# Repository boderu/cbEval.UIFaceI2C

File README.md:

# cbEval.UIFaceI2C
I2C-Bus User-Interface für das Camdenboss-System.

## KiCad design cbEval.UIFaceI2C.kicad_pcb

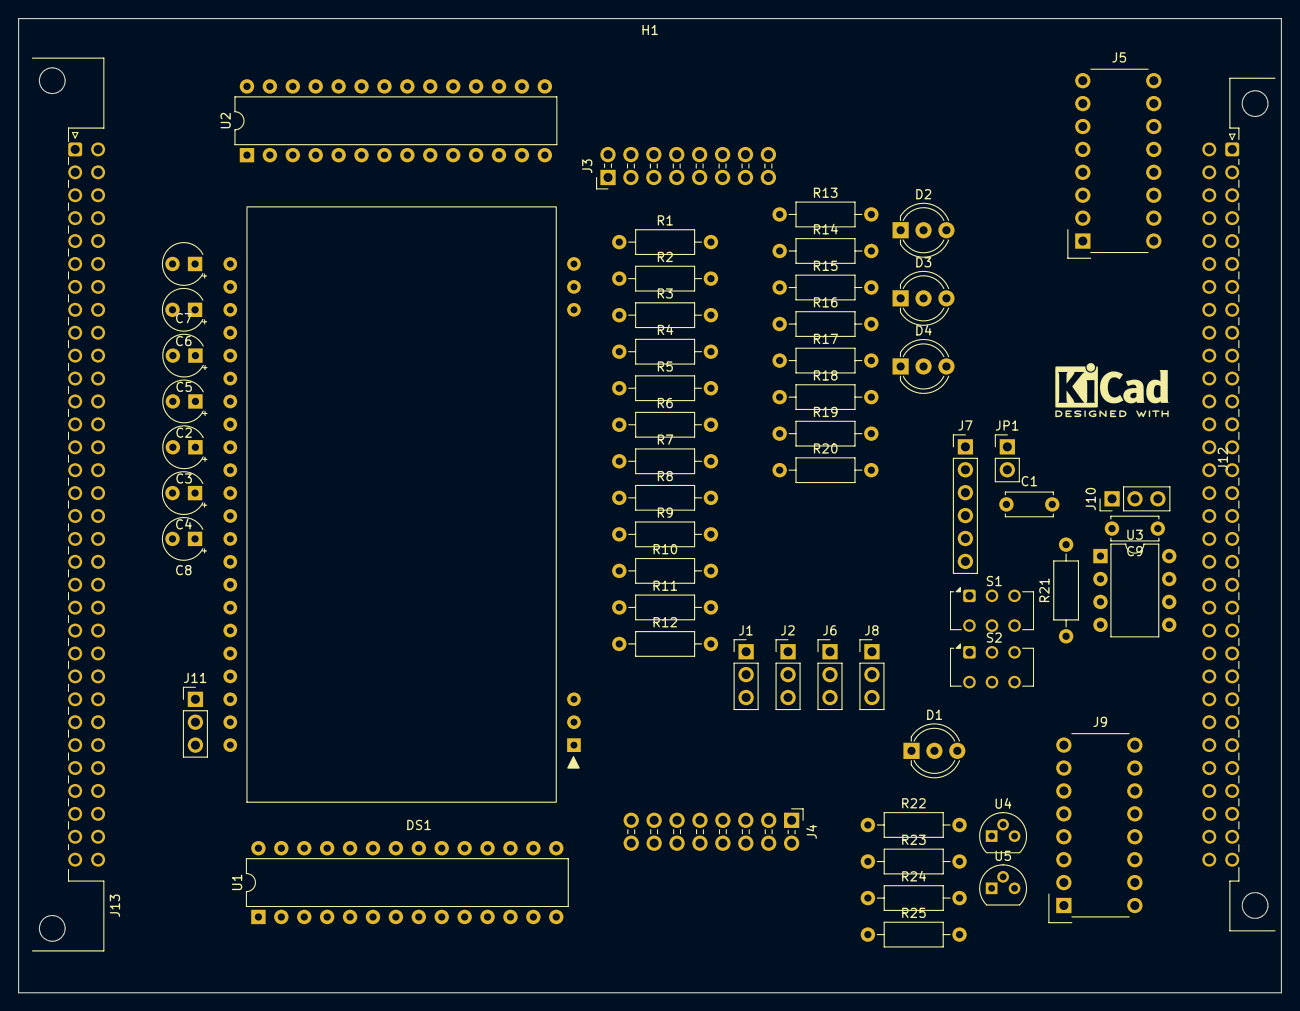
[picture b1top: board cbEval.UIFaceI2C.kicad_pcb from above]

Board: 2 copper layers, 140.0 x 108.0 mm, 62 parts (0 on the bottom side), 59 nets, no tracks yet.

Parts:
C1: 4n7; C_Disc_D5.0mm_W2.5mm_P5.08mm
C2, C3, C4, C5, C6, C7, C8: 1µ; CP_Radial_Tantal_D4.5mm_P2.50mm
C9: 100n; C_Disc_D5.0mm_W2.5mm_P5.08mm
D1, D2, D3, D4: MV5439A; LED_D5.0mm-3
DS1: EA DOGM204W-A; EA-DOGM204-A
H1: CIME.E.BE3500S.4x; Camdenboss.CIME.E.BE3500S.4x
J1, J2, J6, J8, J10, J11: Bergstik-II_1x3; PinHeader_1x03_P2.54mm_Vertical
J3, J4: Header.Hor.2x8.9-103326-0-08; PinHeader_2x08_P2.54mm_Horizontal
J5, J9: Socket.Hor.2x8.1-5535512-8; Socket.Hor.2x5.6-5535512-4
J7: Bergstik-II_1x6; PinHeader_1x06_P2.54mm_Vertical
J12: DIN41612.B.2x32.Male.Horizontal.THT
J13: DIN41612.B.2x32.Female.Horizontal.THT
JP1: Bergstik-II_2; PinHeader_1x02_P2.54mm_Vertical
MP1: KiCAD-DesignedWith-Logo2.5mm.SilkScreen; KiCad-Logo2_5mm_SilkScreen
R1, R2, R3, R6, R9, R10, R12, R21: 10K; R_Axial_DIN0207_L6.3mm_D2.5mm_P10.16mm_Horizontal
R4, R5, R24, R25: 47K5; R_Axial_DIN0207_L6.3mm_D2.5mm_P10.16mm_Horizontal
R7, R8: 60R4; R_Axial_DIN0207_L6.3mm_D2.5mm_P10.16mm_Horizontal
R11: 4K7; R_Axial_DIN0207_L6.3mm_D2.5mm_P10.16mm_Horizontal
R13, R14, R15, R16, R17, R18, R19, R20: 1K; R_Axial_DIN0207_L6.3mm_D2.5mm_P10.16mm_Horizontal
R22: 24R; R_Axial_DIN0207_L6.3mm_D2.5mm_P10.16mm_Horizontal
R23: 18R; R_Axial_DIN0207_L6.3mm_D2.5mm_P10.16mm_Horizontal
S1, S2: C&K-JS202011; SW_CK_JS202011CQN_DPDT_Straight
U1, U2: MCP23017-E/SP; DIP-28_W7.62mm
U3: ATtiny85-20PU; DIP-8_W7.62mm
U4, U5: TN0702N3-G; TO-92

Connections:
+3V3: J4.3, J5.3
+5V: J4.5, J5.5
+15V: J4.4, J5.4
+VDC: J4.7, J5.7
-15V: J4.6, J5.6
/Busses/CAN-H: J1.1 (A1), J3.3, J9.3, S1.2 (B)
/Busses/CAN-L: J1.3 (A3), J3.4, J9.4, S1.5 (B)
/Busses/I2C-SCL: J4.10, J5.10, J6.3 (A3), S2.5 (B)
/Busses/I2C-SDA: J4.9, J5.9, J6.2 (A2), S2.2 (B)
/Busses/One-Wire: J3.16, J7.6 (A6), J9.16, R11.2
/Busses/Reserved0: J3.7, J8.1 (A1), J9.7
/Busses/Reserved1: J3.8, J8.3 (A3), J9.8
/Busses/SPI-ADR0: J2.1 (A1), J3.13, J9.13, R1.1
/Busses/SPI-ADR1: J2.2 (A2), J3.14, J9.14, R2.1
/Busses/SPI-ADR2: J2.3 (A3), J3.15, J9.15, R3.1
/Busses/SPI-CLK: J3.11, J7.3 (A3), J9.11, R10.1
/Busses/SPI-MRST: J3.10, J7.2 (A2), J9.10, R9.1
/Busses/SPI-MTSR: J3.9, J7.1 (A1), J9.9, R6.1
/Busses/SPI-~CE: J3.12, J7.4 (A4), J9.12, R12.2
/Busses/~RESET: J4.8, J5.8, J6.1 (A1)
/Display/I2C-SDA: DS1.38 (I2C-SDA), DS1.39 (I2C-SDA)
/Display/LCD-BG-GN: R25.1, U4.2 (G)
/Display/LCD-BG-RD: R24.1, U5.2 (G)
/LED.GN0: R14.2, U1.22 (GPA1)
/LED.GN1: R16.2, U1.24 (GPA3)
/LED.GN2: R18.2, U1.26 (GPA5)
/LED.GN3: R20.2, U1.28 (GPA7)
/LED.RD0: R13.2, U1.21 (GPA0)
/LED.RD1: R15.2, U1.23 (GPA2)
/LED.RD2: R17.2, U1.25 (GPA4)
/LED.RD3: R19.2, U1.27 (GPA6)
GND: C1.2, C2.2, C3.2, C4.2, C5.2, C6.2, C7.2, C8.2, C9.2, DS1.29 (IM2), DS1.30 (IM1), DS1.32 (VSS), J1.2 (A2), J3.1, J3.2, J3.5, J3.6, J4.11, J4.12, J4.13, J4.14, J4.15, J4.16, J5.11, J5.12, J5.13, J5.14, J5.15, J5.16, J7.5 (A5), J8.2 (A2), J9.1, J9.2, J9.5, J9.6, J10.2 (A2), J11.3 (A3), R1.2, R2.2, R3.2, R6.2, R9.2, R10.2, R24.2, R25.2, U3.4 (GND), U4.1 (S), U5.1 (S)
unnamed: C1.1, R7.1, R8.1
unnamed: D1.3 (C-GN), R14.1
unnamed: D1.1 (C-RD), R13.1
unnamed: D2.3 (C-GN), R16.1
unnamed: D2.1 (C-RD), R15.1
unnamed: D3.3 (C-GN), R18.1
unnamed: D3.1 (C-RD), R17.1
unnamed: D4.3 (C-GN), R20.1
unnamed: D4.1 (C-RD), R19.1
unnamed: DS1.20 (CR), R22.1
unnamed: DS1.21 (CG), R23.1
unnamed: DS1.43 (I2C-SA0), J11.2 (A2)
unnamed: C3.1, DS1.24 (V0)
unnamed: C4.1, DS1.25 (V1)
unnamed: C5.1, DS1.26 (V2)
unnamed: C6.1, DS1.27 (V3)
unnamed: C7.1, DS1.28 (V4)
unnamed: C2.1, DS1.23 (VOUT)
unnamed: J10.1 (A1), R21.2, U3.1 (dW)
unnamed: JP1.2 (B), R11.1
unnamed: R7.2, S1.3 (C)
unnamed: R8.2, S1.6 (C)
unnamed: R4.1, S2.3 (C)
unnamed: R5.1, S2.6 (C)
unnamed: R23.2, U4.3 (D)
unnamed: R22.2, U5.3 (D)
VCC: C8.1, C9.1, D1.2 (A), D2.2 (A), D3.2 (A), D4.2 (A), DS1.1 (AGR), DS1.31 (VDD), DS1.33 (D7), DS1.34 (D6), DS1.35 (D5), DS1.36 (D4), DS1.37 (D3), DS1.41 (E), DS1.42 (R/~W), J4.1, J4.2, J5.1, J5.2, J10.3 (A3), J11.1 (A1), JP1.1 (A), R4.2, R5.2, R12.1, R21.1, U3.8 (VCC)

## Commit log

2024-02-26 Zwischenstand
2024-03-02 Bauteile aktualisiert
